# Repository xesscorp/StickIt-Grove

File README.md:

# StickIt!-Grove

# Description

The StickIt!-Grove lets you use Grove modules with your XESS programmable logic boards and the StickIt! mainboard.

* License: [CC BY 4.0](http://creativecommons.org/licenses/by/4.0/legalcode)
* Documentation: [StickIt-Grove.readthedocs.org](https://StickIt-Grove.readthedocs.org)

# Features

* Four independent sockets for Grove modules.
* PMOD compatible.
* Solderless breadboard compatible.
* Open-source design.

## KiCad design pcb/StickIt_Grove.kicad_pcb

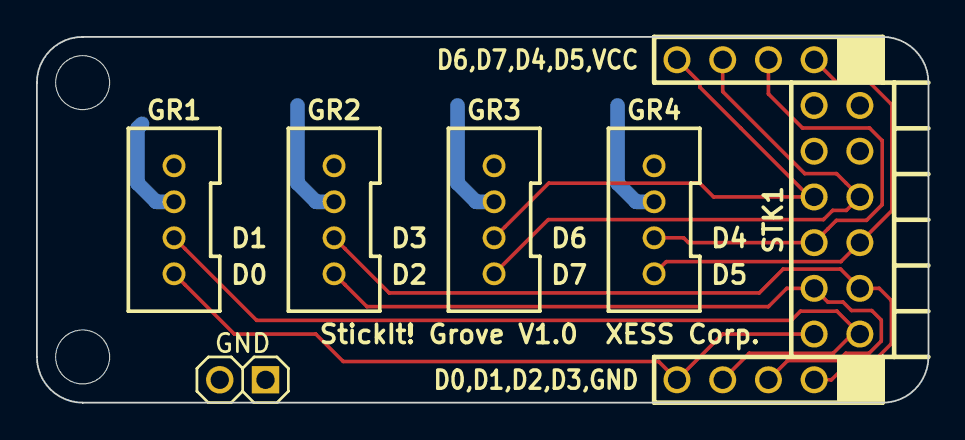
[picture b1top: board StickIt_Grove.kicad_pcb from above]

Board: 2 copper layers, 49.5 x 20.3 mm, 6 parts (0 on the bottom side), 10 nets.

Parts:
GR1, GR2, GR3, GR4: Grove_Male; GROVE_MALE
JP1: JUMPER; HDR_1x2
STK1: STICKIT2_HDR

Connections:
D0: GR1.1, STK1.D0
D1: GR1.2, STK1.D1
D2: GR2.1, STK1.D2
D3: GR2.2, STK1.D3
D4: GR4.2, STK1.D4
D5: GR4.1, STK1.D5
D6: GR3.2, STK1.D6
D7: GR3.1, STK1.D7
GND: GR1.4, GR2.4, GR3.4, GR4.4, JP1.1, JP1.2, STK1.GND
VCC: GR1.3, GR2.3, GR3.3, GR4.3, STK1.VCC

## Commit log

2015-07-15 Initial commit for V1.0.
2015-07-15 Corrected the readthedocs documentation files.
2015-07-15 Corrected link to readthedocs.org.
2015-07-15 Moved mkdocs.yml up one directory so readthedocs.org would process it correctly.

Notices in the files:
pcb/StickIt_Grove.kicad_pcb:
(c) 2015
